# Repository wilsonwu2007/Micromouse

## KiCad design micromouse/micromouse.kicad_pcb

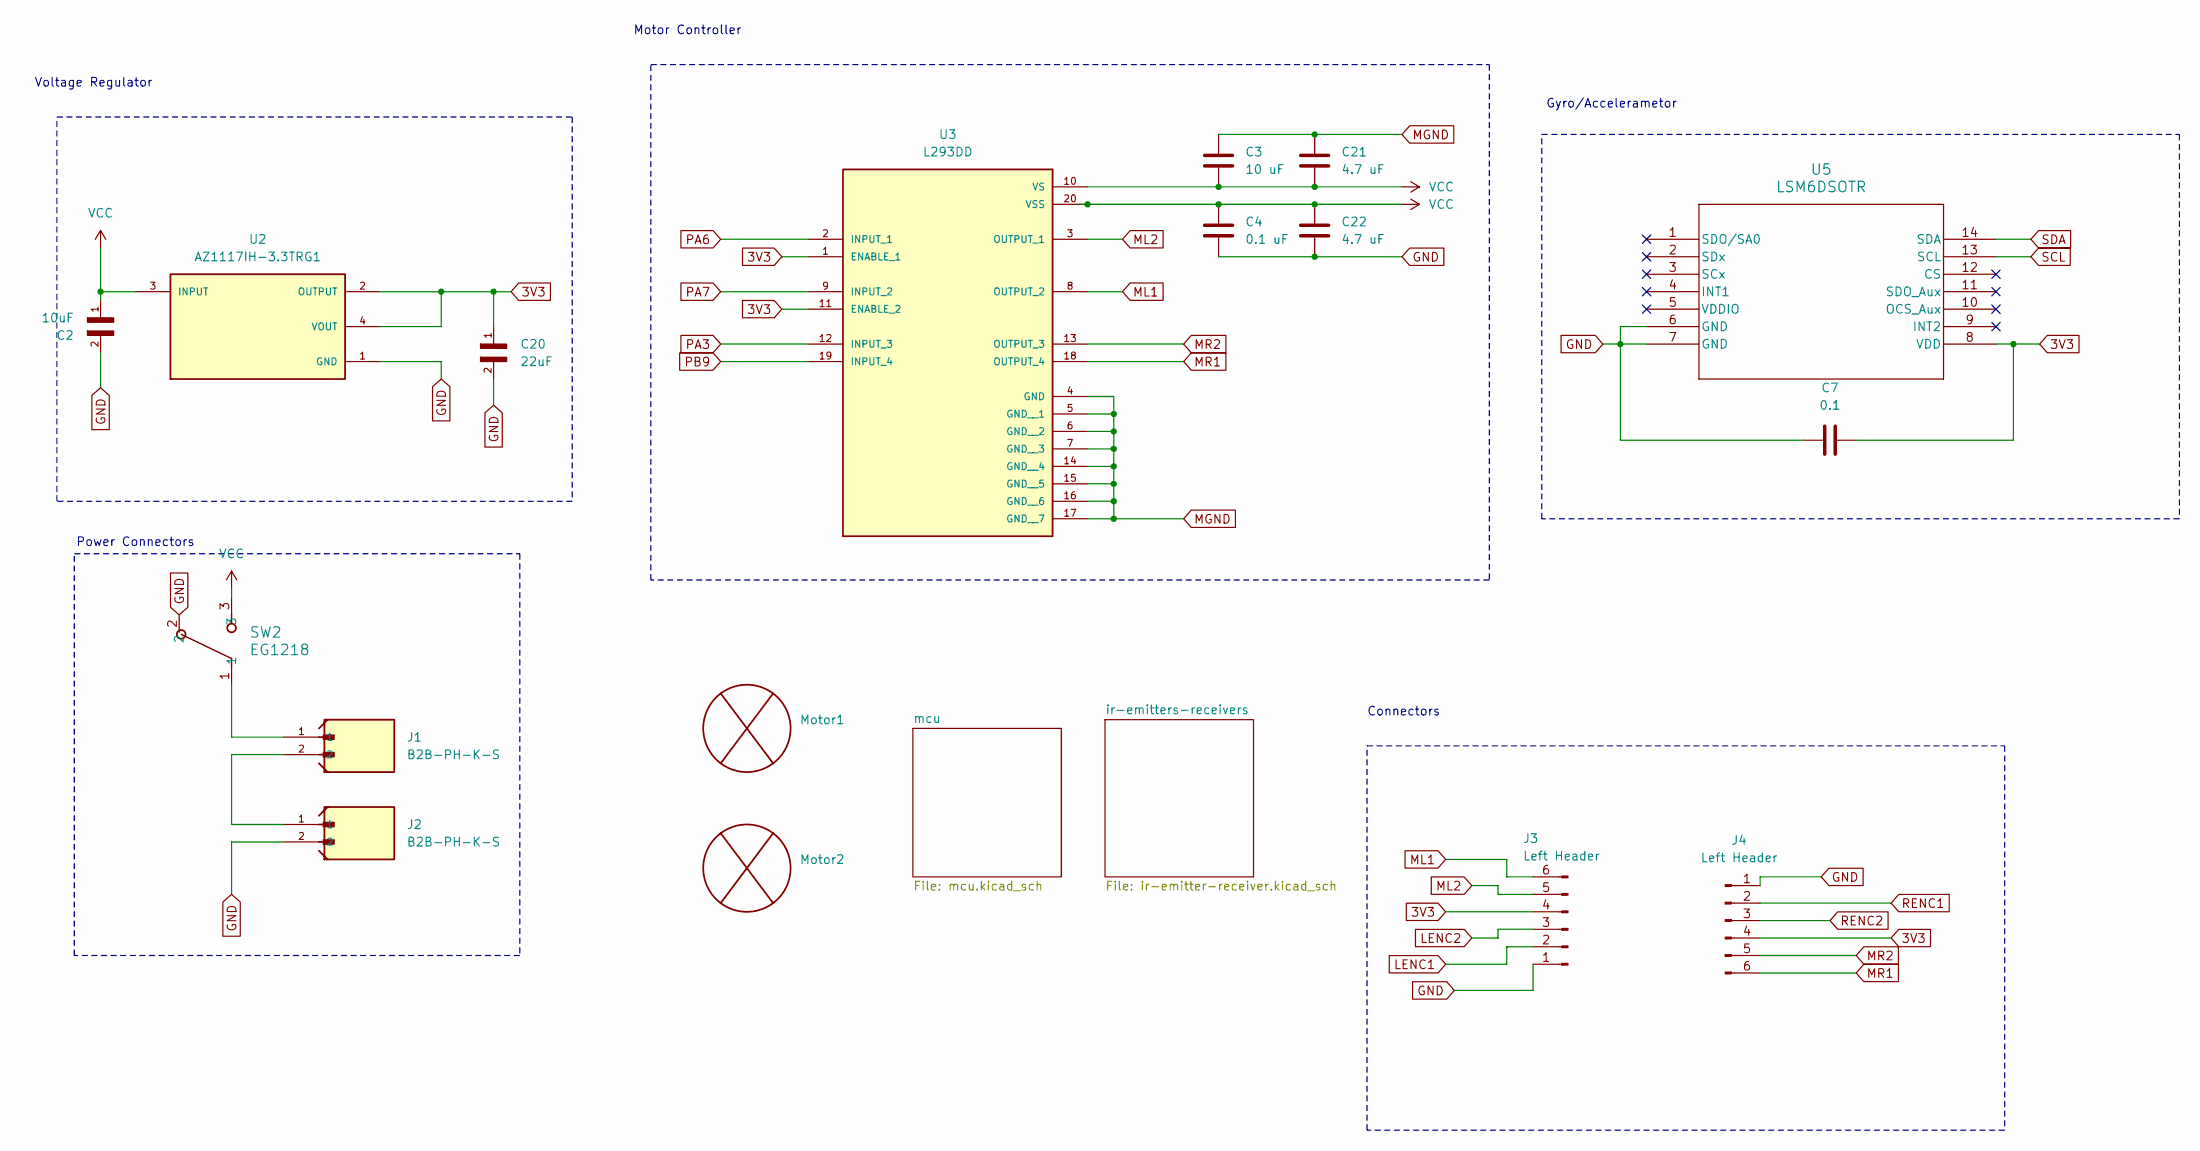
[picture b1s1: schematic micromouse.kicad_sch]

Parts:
C2: 10uF; C_0805_2012Metric
C3: 10 uF; C_0805_2012Metric
C4: 0.1 uF; C_0805_2012Metric
C7: 0.1; C_0805_2012Metric
C20: 22uF; C_0805_2012Metric
C21, C22: 4.7 uF; C_0805_2012Metric
J1, J2: B2B-PH-K-S; JST_PH_B2B-PH-K_1x02_P2.00mm_Vertical
J3, J4: Left Header; SULLINS_PPTC061LFBN-RC
Motor1, Motor2: Pololu_Motor
SW2: EG1218; SW_1218_EWI
U2: AZ1117IH-3.3TRG1; SOT230P700X185-4N; PARTREV 2-2
U3: L293DD; SOIC127P1032X265-20N; PARTREV N/A
U5: LSM6DSOTR; LGA-14L_2P5X3X0P86_STM

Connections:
3V3: C7.2, C20.1, J3.4, J4.4, U2.2 (OUTPUT), U2.4 (VOUT), U3.1 (ENABLE_1), U3.11 (ENABLE_2), U5.8 (VDD); also elsewhere on the board
LENC1: J3.2; also elsewhere on the board
LENC2: J3.3; also elsewhere on the board
ML1: J3.6, U3.8 (OUTPUT_2)
ML2: J3.5, U3.3 (OUTPUT_1)
MR1: J4.6, U3.18 (OUTPUT_4)
MR2: J4.5, U3.13 (OUTPUT_3)
unnamed: J1.1, SW2.1
unnamed: J1.2, J2.1
PA3: U3.12 (INPUT_3); also elsewhere on the board
PA6: U3.2 (INPUT_1); also elsewhere on the board
PA7: U3.9 (INPUT_2); also elsewhere on the board
PB9: U3.19 (INPUT_4); also elsewhere on the board
RENC1: J4.2; also elsewhere on the board
RENC2: J4.3; also elsewhere on the board
SCL: U5.13 (SCL); also elsewhere on the board
SDA: U5.14 (SDA); also elsewhere on the board
VCC: C2.1, C3.2, C4.1, C21.2, C22.1, SW2.3, U2.3 (INPUT), U3.10 (VS), U3.20 (VSS)

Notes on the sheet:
Power Connectors
Voltage Regulator
Gyro/Accelerametor
Connectors
Motor Controller

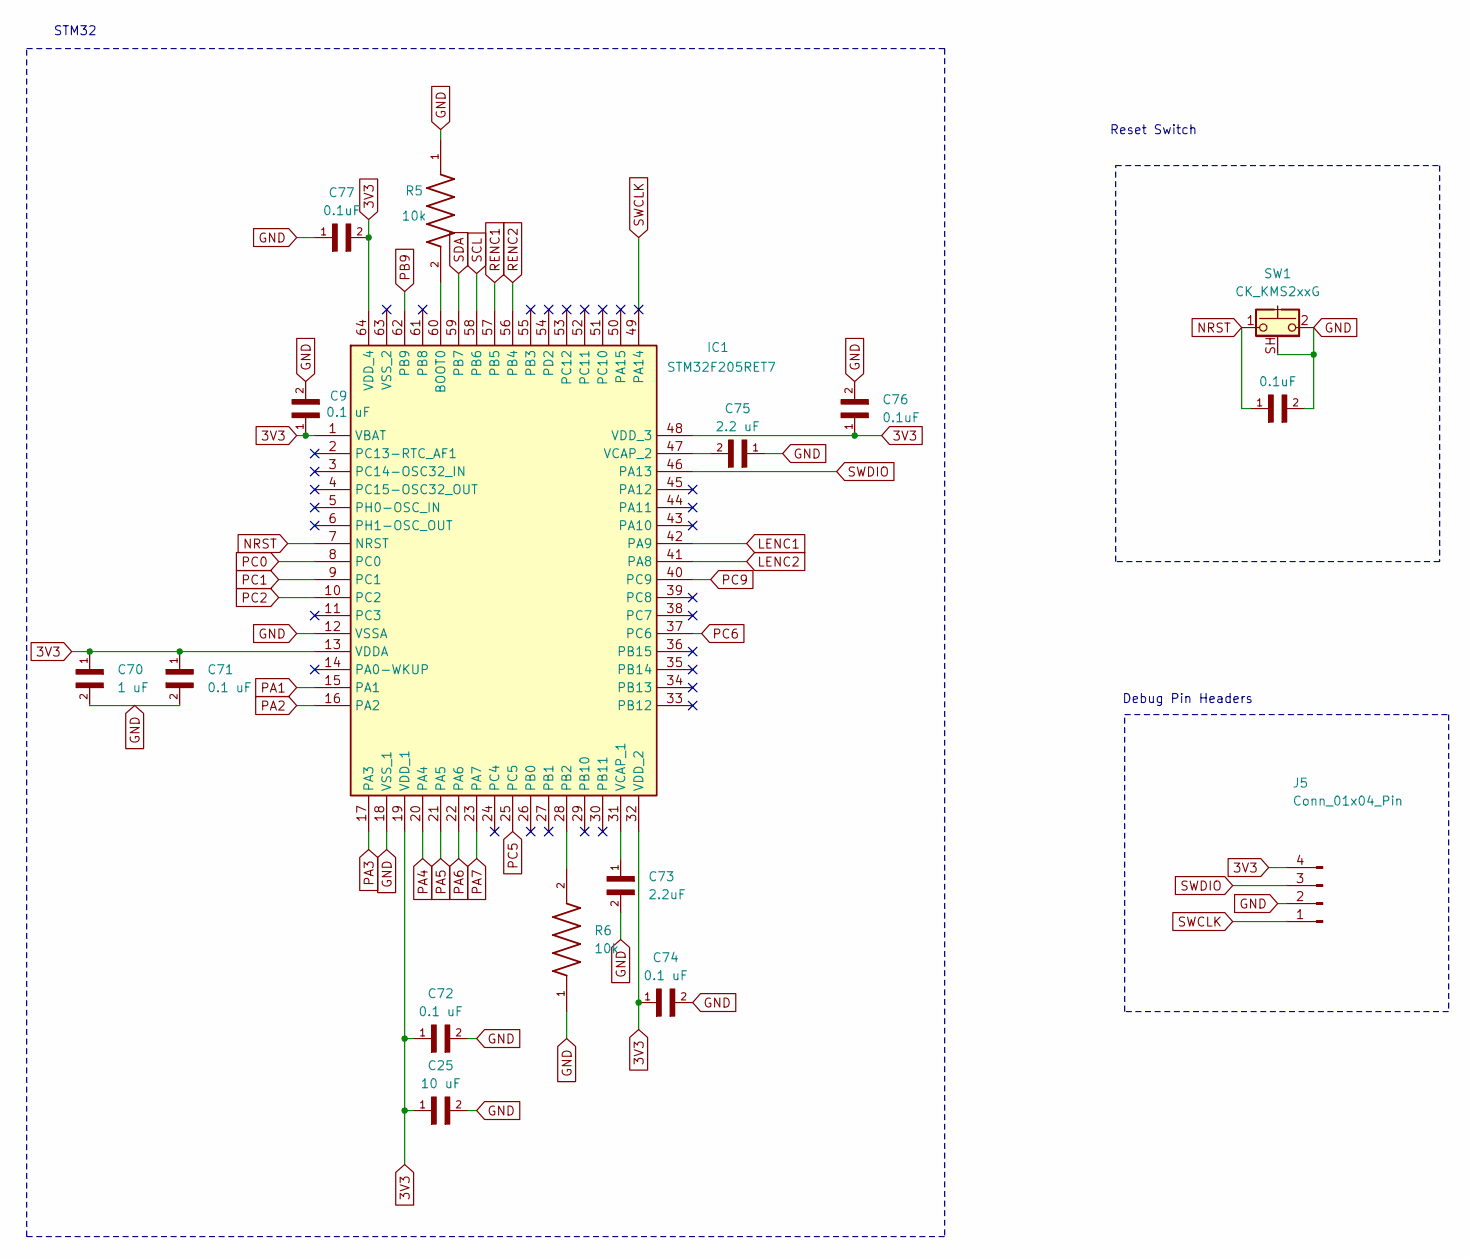
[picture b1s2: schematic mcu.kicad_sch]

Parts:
C9, C71, C72, C74: 0.1 uF; C_0805_2012Metric
C11, C76, C77: 0.1uF; C_0805_2012Metric
C25: 10 uF; C_0805_2012Metric
C70: 1 uF; C_0805_2012Metric
C73: 2.2uF; C_0805_2012Metric
C75: 2.2 uF; C_0805_2012Metric
IC1: STM32F205RET7; QFP50P1200X1200X160-64N; Manufacturer_Part_Number STM32F205RET7; Mouser Part Number 511-STM32F205RET7
J5: Conn_01x04_Pin; PinHeader_1x04_P2.54mm_Vertical
R5, R6: 10k; R_0805_2012Metric
SW1: CK_KMS2xxG; SW_SPST_CK_KMS2xxGP

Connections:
3V3: C9.1, C25.1, C70.1, C71.1, C72.1, C74.1, C76.1, C77.2, IC1.1 (VBAT), IC1.13 (VDDA), IC1.19 (VDD_1), IC1.32 (VDD_2), IC1.48 (VDD_3), IC1.64 (VDD_4), J5.4; also elsewhere on the board
LENC1: IC1.42 (PA9); also elsewhere on the board
LENC2: IC1.41 (PA8); also elsewhere on the board
NRST: C11.1, IC1.7 (NRST), SW1.1
unnamed: IC1.60 (BOOT0), R5.2
unnamed: IC1.28 (PB2), R6.2
unnamed: C73.1, IC1.31 (VCAP_1)
unnamed: C75.2, IC1.47 (VCAP_2)
PA1: IC1.15 (PA1); also elsewhere on the board
PA2: IC1.16 (PA2); also elsewhere on the board
PA3: IC1.17 (PA3); also elsewhere on the board
PA4: IC1.20 (PA4)
PA5: IC1.21 (PA5)
PA6: IC1.22 (PA6); also elsewhere on the board
PA7: IC1.23 (PA7); also elsewhere on the board
PB9: IC1.62 (PB9); also elsewhere on the board
PC1: IC1.9 (PC1); also elsewhere on the board
PC2: IC1.10 (PC2); also elsewhere on the board
PC5: IC1.25 (PC5); also elsewhere on the board
PC9: IC1.40 (PC9); also elsewhere on the board
RENC1: IC1.57 (PB5); also elsewhere on the board
RENC2: IC1.56 (PB4); also elsewhere on the board
SCL: IC1.58 (PB6); also elsewhere on the board
SDA: IC1.59 (PB7); also elsewhere on the board
SWCLK: IC1.49 (PA14), J5.1
SWDIO: IC1.46 (PA13), J5.3

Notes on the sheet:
STM32
Reset Switch
Debug Pin Headers

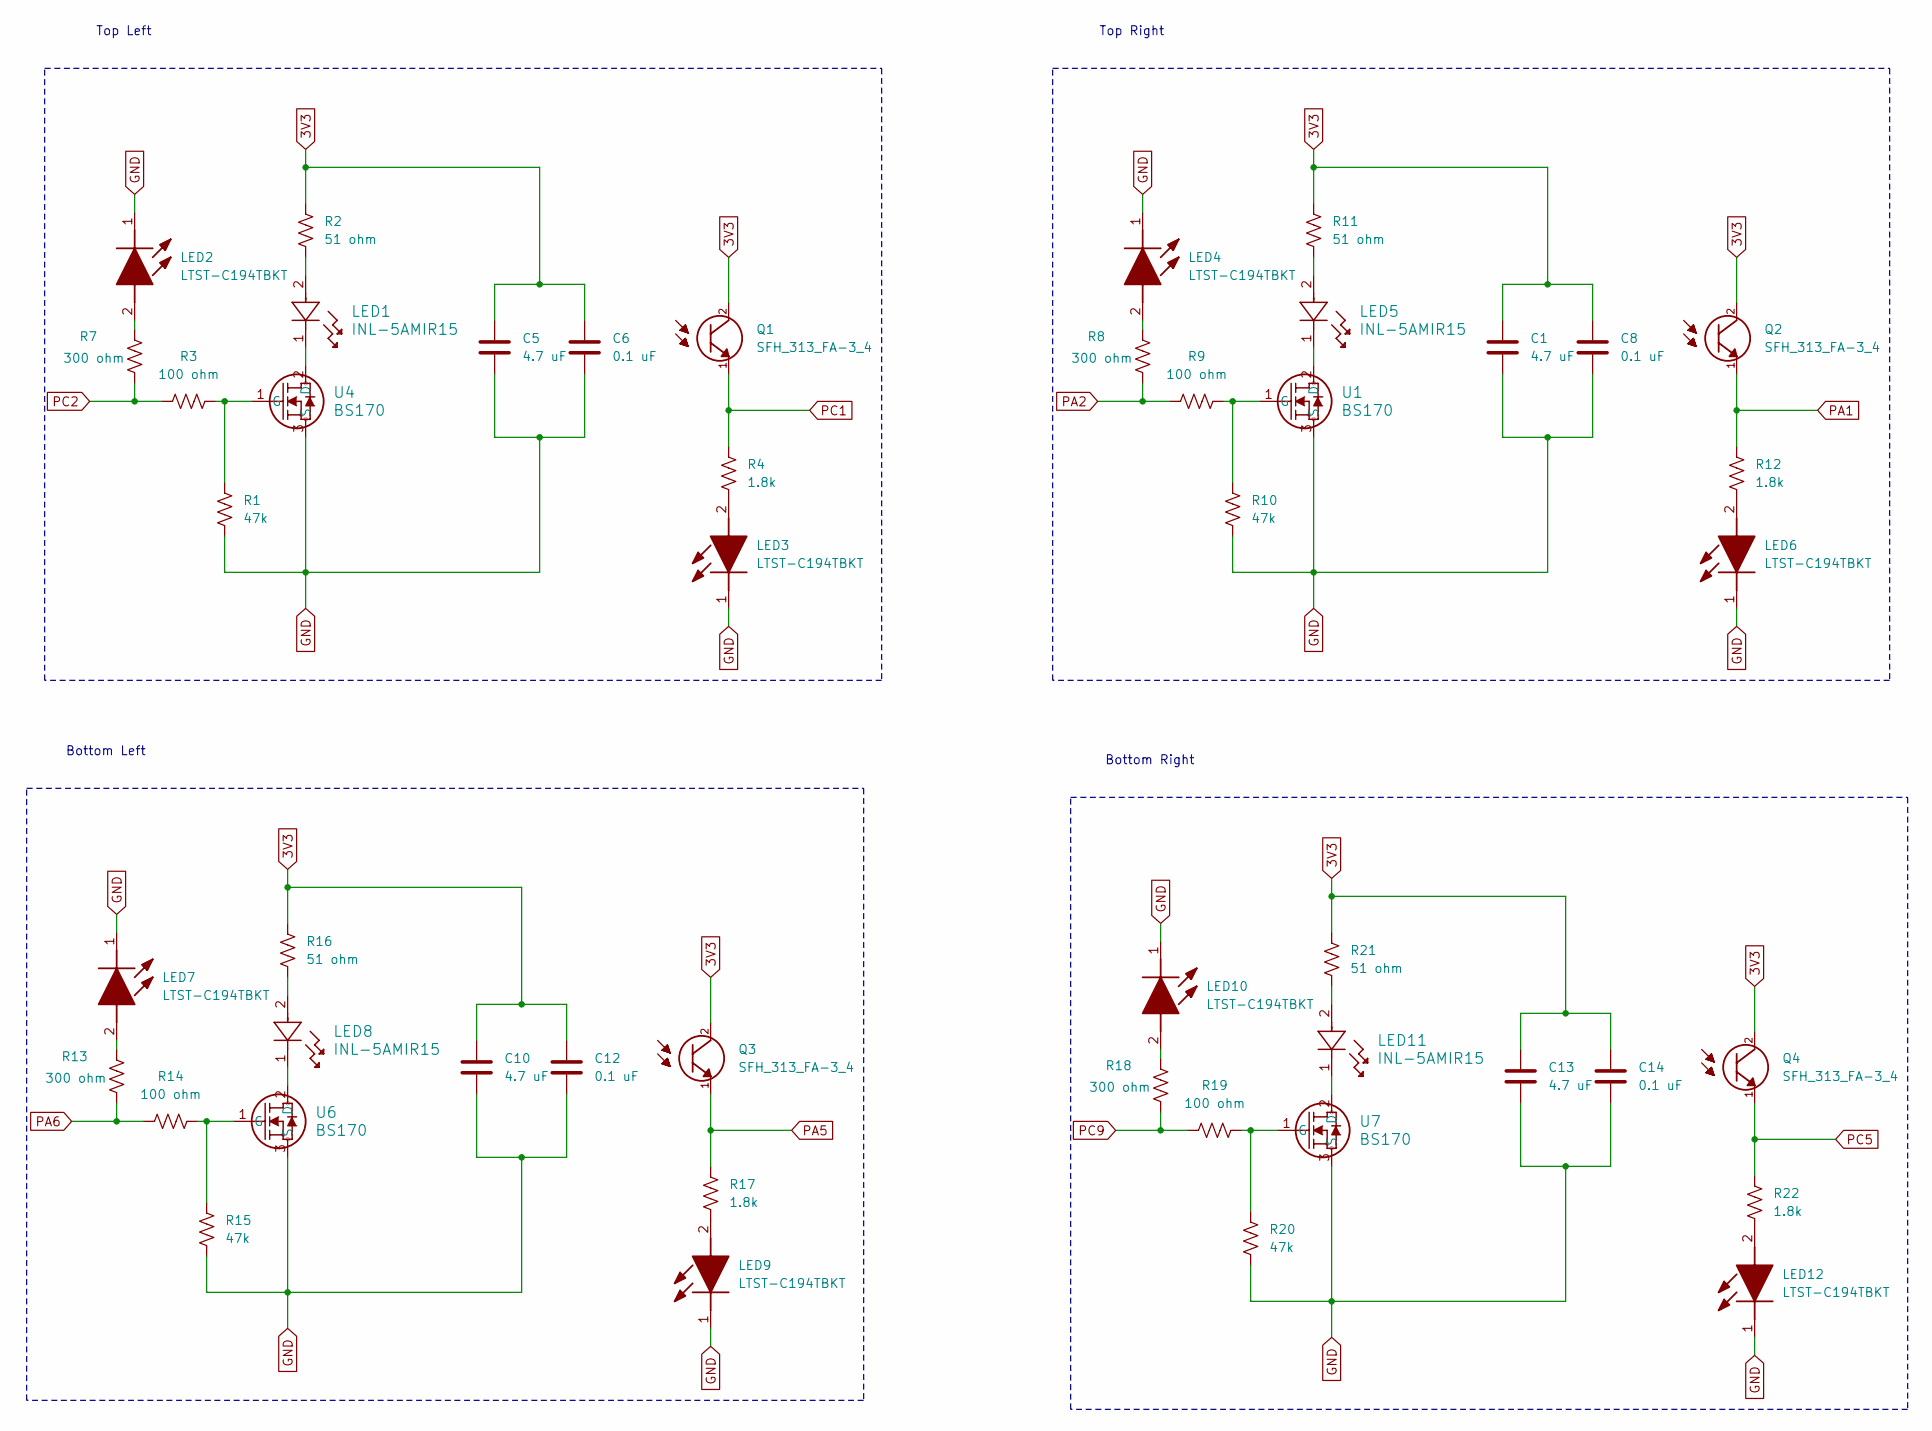
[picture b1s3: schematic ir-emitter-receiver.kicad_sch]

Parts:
C1, C5, C10, C13: 4.7 uF; C_0805_2012Metric
C6, C8, C12, C14: 0.1 uF; C_0805_2012Metric
LED1, LED5, LED8, LED11: INL-5AMIR15; LED_INL-5AMIR15_INO
LED2, LED3, LED4, LED6, LED7, LED9, LED10, LED12: LTST-C194TBKT; LEDC1608X35N; Mouser Part Number 859-LTST-C194TBKT
Q1, Q2, Q3, Q4: SFH_313_FA-3_4; XDCR_SFH_313_FA-3_4; PARTREV 1.3
R1, R10, R15, R20: 47k; R_0805_2012Metric
R2, R11, R16, R21: 51 ohm; R_0805_2012Metric
R3, R9, R14, R19: 100 ohm; R_0805_2012Metric
R4, R12, R17, R22: 1.8k; R_0805_2012Metric
R7, R8, R13, R18: 300 ohm; R_0805_2012Metric
U1, U4, U6, U7: BS170; TO_SA06_ONS

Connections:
3V3: C1.1, C5.1, C6.1, C8.1, C10.1, C12.1, C13.1, C14.1, Q1.2, Q2.2, Q3.2, Q4.2, R2.1, R11.1, R16.1, R21.1; also elsewhere on the board
unnamed 14: LED1.1, U4.2 (D); also elsewhere on the board
unnamed: LED1.2, R2.2
unnamed: LED2.2 (A), R7.2
unnamed: LED3.2 (A), R4.2
unnamed: LED4.2 (A), R8.2
unnamed 19: LED5.1, U1.2 (D); also elsewhere on the board
unnamed: LED5.2, R11.2
unnamed: LED6.2 (A), R12.2
unnamed: LED7.2 (A), R13.2
unnamed 23: LED8.1, U6.2 (D); also elsewhere on the board
unnamed: LED8.2, R16.2
unnamed: LED9.2 (A), R17.2
unnamed: LED10.2 (A), R18.2
unnamed 27: LED11.1, U7.2 (D); also elsewhere on the board
unnamed: LED11.2, R21.2
unnamed: LED12.2 (A), R22.2
unnamed 30: R1.1, R3.2, U4.1 (G); also elsewhere on the board
unnamed 31: R9.2, R10.1, U1.1 (G); also elsewhere on the board
unnamed 32: R19.2, R20.1, U7.1 (G); also elsewhere on the board
unnamed 33: R14.2, R15.1, U6.1 (G); also elsewhere on the board
PA1: Q2.1, R12.1; also elsewhere on the board
PA2: R8.1, R9.1; also elsewhere on the board
PC1: Q1.1, R4.1; also elsewhere on the board
PC2: R3.1, R7.1; also elsewhere on the board
PC5: Q4.1, R22.1; also elsewhere on the board
PC9: R18.1, R19.1; also elsewhere on the board

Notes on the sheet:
Bottom Left
Bottom Right
Top Right
Top Left

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
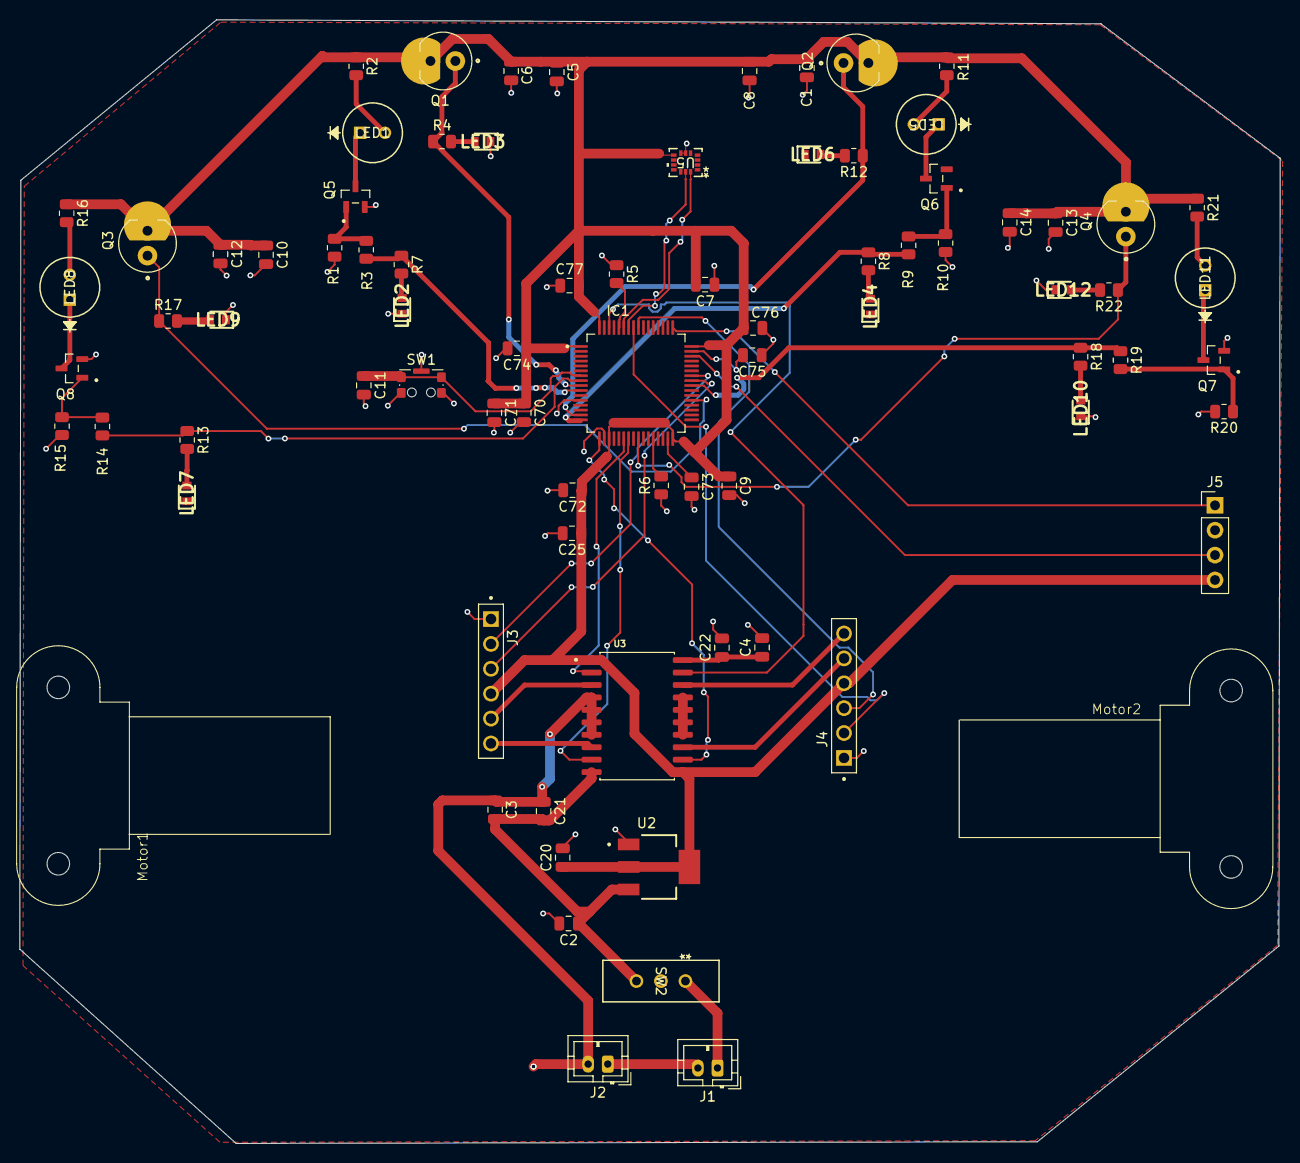
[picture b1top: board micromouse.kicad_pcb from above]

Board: 2 copper layers, 128.6 x 114.7 mm, 81 parts (0 on the bottom side), 55 nets.

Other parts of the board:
Q5, Q6, Q7, Q8: 2N7002LT1G; SOT95P240X111-3N

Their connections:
unnamed 14: Q5.3; also elsewhere on the board
unnamed 19: Q6.3; also elsewhere on the board
unnamed 23: Q8.3; also elsewhere on the board
unnamed 27: Q7.3; also elsewhere on the board
unnamed 30: Q5.1; also elsewhere on the board
unnamed 31: Q6.1; also elsewhere on the board
unnamed 32: Q7.1; also elsewhere on the board
unnamed 33: Q8.1; also elsewhere on the board

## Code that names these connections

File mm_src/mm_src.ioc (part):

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Mcu.Name=STM32F205R(B-C-E-F-G)Tx
Mcu.Package=LQFP64
Mcu.UserName=STM32F205RETx
PA1.Signal=ADCx_IN1
PA13.Mode=Serial_Wire
PA13.Signal=SYS_JTMS-SWDIO
PA14.Mode=Serial_Wire
PA14.Signal=SYS_JTCK-SWCLK
PA2.Signal=GPIO_Output
PA3.Signal=ADCx_IN3
PA6.Signal=S_TIM13_CH1
PA7.Signal=S_TIM14_CH1
PA8.Signal=S_TIM1_CH1
PA9.Signal=S_TIM1_CH2
PB11.Signal=S_TIM2_CH4
PB4.Signal=S_TIM3_CH1
PB6.Mode=I2C
PB6.Signal=I2C1_SCL
PB7.Mode=I2C
PB7.Signal=I2C1_SDA
PB9.Signal=S_TIM4_CH4
PC0.Signal=GPIO_Output
PC1.Signal=ADCx_IN11
PC2.Signal=GPIO_Output
PC5.Signal=ADCx_IN15
PC6.Signal=GPIO_Input
PC7.Signal=S_TIM3_CH2
PC9.Signal=GPIO_Output
PH0-OSC_IN.Mode=HSE-External-Oscillator
PH0-OSC_IN.Signal=RCC_OSC_IN
PH1-OSC_OUT.Mode=HSE-External-Oscillator
PH1-OSC_OUT.Signal=RCC_OSC_OUT
RCC.HSE_VALUE=25000000
RCC.SYSCLKFreq_VALUE=120000000
RCC.SYSCLKSource=RCC_SYSCLKSOURCE_PLLCLK
board=custom

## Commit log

2026-01-29 added files
2026-01-31 added mpu 6050 schematic
2026-03-02 sch updates
2026-03-06 updated footprints and schematic
2026-03-06 subsystem grouping
2026-03-06 Revision + adding motors
    changes to schematic and pcb layout
2026-03-08 updates to layout
2026-03-25 pcb updates
2026-04-02 PCB Change
    routed MGND to GND
2026-04-03 updated pcb
    routed mgnd to gnd
2026-04-03 pcb changes
    final ver 1
2026-04-03 final
2026-04-08 file management
2026-05-04 created stm32 project
2026-05-11 pid control and motor code
